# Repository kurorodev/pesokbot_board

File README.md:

# Pesok Robot Board - робототехническая платформа.

## Архитектура

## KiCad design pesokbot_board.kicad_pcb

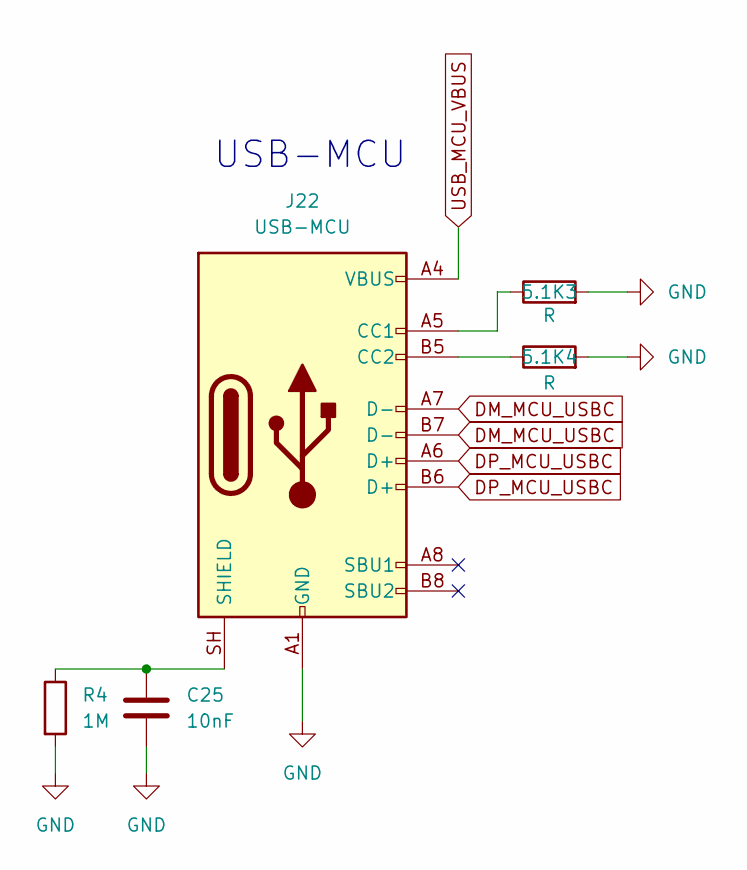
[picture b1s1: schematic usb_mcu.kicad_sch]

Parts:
5.1K3, 5.1K4: R; R_0805_2012Metric_Pad1.20x1.40mm_HandSolder
C25: 10nF; C_0805_2012Metric_Pad1.18x1.45mm_HandSolder
J22: USB-MCU; USB_C_Receptacle_HRO_TYPE-C-31-M-12
R4: 1M; R_0805_2012Metric_Pad1.20x1.40mm_HandSolder

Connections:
DM_MCU_USBC: J22.A7 (D-), J22.B7 (D-)
DP_MCU_USBC: J22.A6 (D+), J22.B6 (D+)
unnamed: 5.1K3.1, J22.A5 (CC1)
unnamed: 5.1K4.1, J22.B5 (CC2)
unnamed: C25.1, J22.SH (SHIELD), R4.1
USB_MCU_VBUS: J22.A4 (VBUS), J22.A9 (VBUS), J22.B4 (VBUS), J22.B9 (VBUS); also elsewhere on the board

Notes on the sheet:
USB-MCU

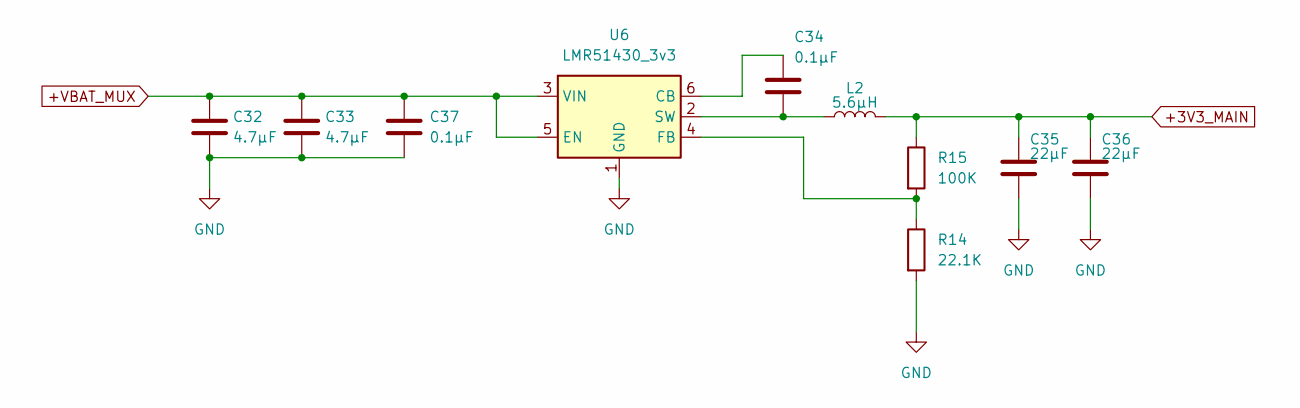
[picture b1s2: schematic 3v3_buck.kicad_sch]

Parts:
C32, C33: 4.7µF; CAPC3216X180N
C34, C37: 0.1µF; CAPC1608X90N
C35, C36: 22µF; CAPC3216X178N
L2: 5.6µH; L_Coilcraft_XAL6060-XXX
R14: 22.1K; R_0201_0603Metric
R15: 100K; R_0201_0603Metric
U6: LMR51430_3v3; SOT-23-6

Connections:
+3V3_MAIN: C35.1, C36.1, L2.2, R15.1
+VBAT_MUX: C32.1, C33.1, C37.1, U6.3 (VIN), U6.5 (EN)
unnamed: C34.1, U6.6 (CB)
unnamed: R14.1, R15.2, U6.4 (FB)
unnamed: C34.2, L2.1, U6.2 (SW)

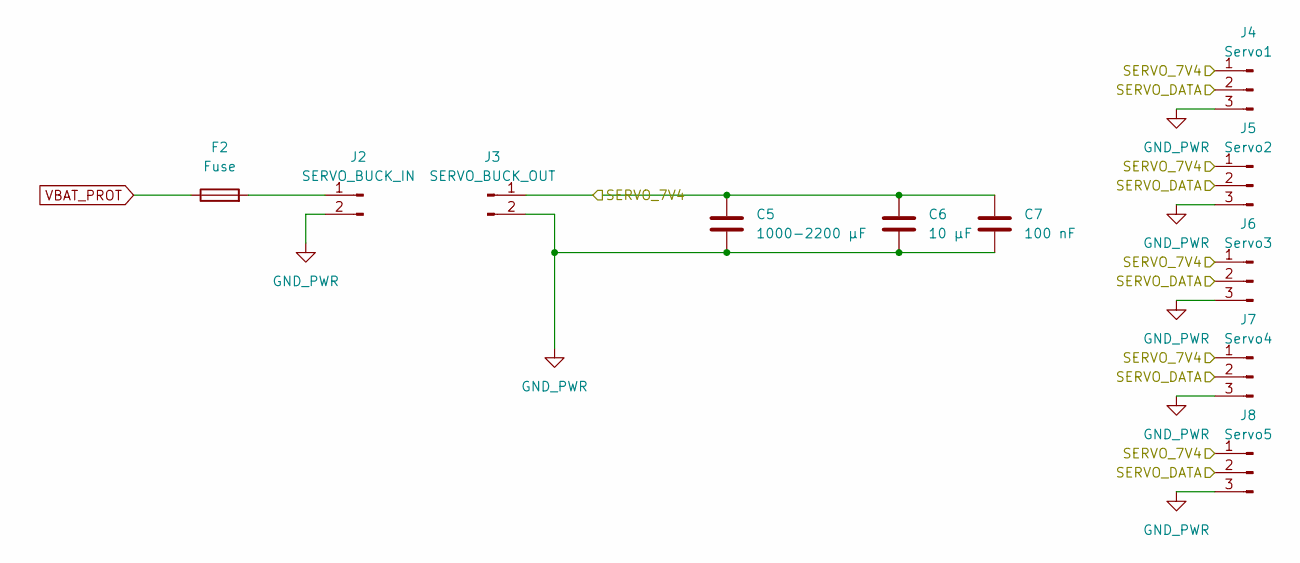
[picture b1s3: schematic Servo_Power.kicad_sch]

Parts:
C5: 1000-2200 µF; C_0805_2012Metric_Pad1.18x1.45mm_HandSolder
C6: 10 µF; C_0805_2012Metric_Pad1.18x1.45mm_HandSolder
C7: 100 nF; CAPC1608X90N
F2: Fuse; Fuse_0805_2012Metric_Pad1.15x1.40mm_HandSolder
J2: SERVO_BUCK_IN
J3: SERVO_BUCK_OUT
J4: Servo1
J5: Servo2
J6: Servo3
J7: Servo4
J8: Servo5

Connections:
GND_PWR: C5.2, C6.2, C7.2, J2.2, J3.2, J4.3, J5.3, J6.3, J7.3, J8.3; also elsewhere on the board
unnamed: C5.1, C6.1, C7.1
unnamed: F2.2, J2.1
unnamed: J3.1, J4.1, J5.1, J6.1, J7.1, J8.1
unnamed: J4.2, J5.2, J6.2, J7.2, J8.2
VBAT_PROT: F2.1; also elsewhere on the board

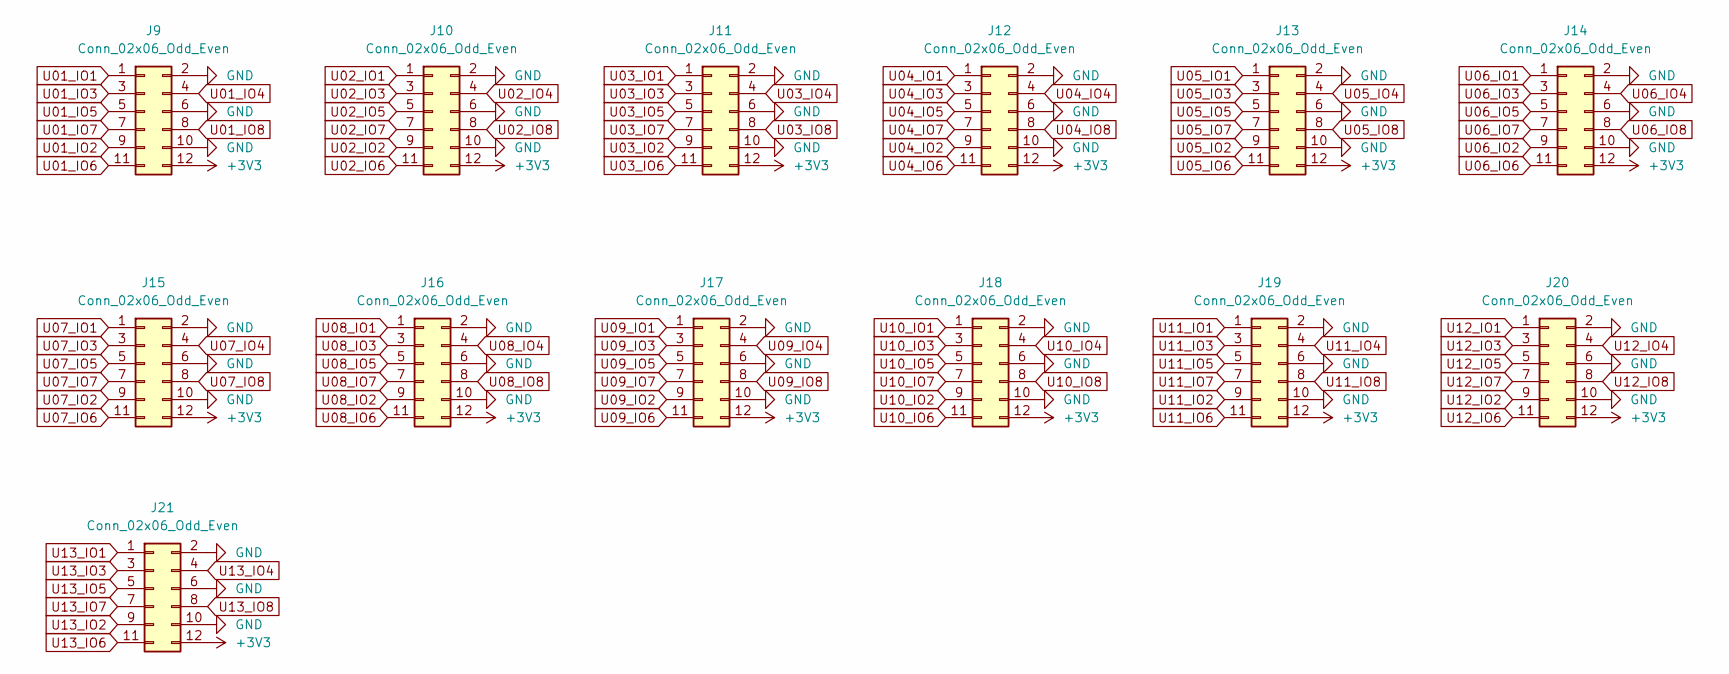
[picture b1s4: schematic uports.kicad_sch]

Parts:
J9, J10, J11, J12, J13, J14, J15, J16, J17, J18, J19, J20, J21: Conn_02x06_Odd_Even; JST_PHD_B12B-PHDSS_2x06_P2.00mm_Vertical

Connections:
+3V3: J9.12, J10.12, J11.12, J12.12, J13.12, J14.12, J15.12, J16.12, J17.12, J18.12, J19.12, J20.12, J21.12; also elsewhere on the board
U01_IO1: J9.1; also elsewhere on the board
U01_IO2: J9.9; also elsewhere on the board
U01_IO3: J9.3; also elsewhere on the board
U01_IO4: J9.4; also elsewhere on the board
U01_IO5: J9.5; also elsewhere on the board
U01_IO6: J9.11; also elsewhere on the board
U01_IO7: J9.7; also elsewhere on the board
U01_IO8: J9.8; also elsewhere on the board
U02_IO1: J10.1; also elsewhere on the board
U02_IO2: J10.9; also elsewhere on the board
U02_IO3: J10.3; also elsewhere on the board
U02_IO4: J10.4; also elsewhere on the board
U02_IO5: J10.5; also elsewhere on the board
U02_IO6: J10.11; also elsewhere on the board
U02_IO7: J10.7; also elsewhere on the board
U02_IO8: J10.8; also elsewhere on the board
U03_IO1: J11.1; also elsewhere on the board
U03_IO2: J11.9; also elsewhere on the board
U03_IO3: J11.3; also elsewhere on the board
U03_IO4: J11.4; also elsewhere on the board
U03_IO5: J11.5; also elsewhere on the board
U03_IO6: J11.11; also elsewhere on the board
U03_IO7: J11.7; also elsewhere on the board
U03_IO8: J11.8; also elsewhere on the board
U04_IO1: J12.1; also elsewhere on the board
U04_IO2: J12.9; also elsewhere on the board
U04_IO3: J12.3; also elsewhere on the board
U04_IO4: J12.4; also elsewhere on the board
U04_IO5: J12.5; also elsewhere on the board
U04_IO6: J12.11; also elsewhere on the board
U04_IO7: J12.7; also elsewhere on the board
U04_IO8: J12.8; also elsewhere on the board
U05_IO1: J13.1; also elsewhere on the board
U05_IO2: J13.9; also elsewhere on the board
U05_IO3: J13.3; also elsewhere on the board
U05_IO4: J13.4; also elsewhere on the board
U05_IO5: J13.5; also elsewhere on the board
U05_IO6: J13.11; also elsewhere on the board
U05_IO7: J13.7; also elsewhere on the board
U05_IO8: J13.8; also elsewhere on the board
U06_IO1: J14.1; also elsewhere on the board
U06_IO2: J14.9; also elsewhere on the board
U06_IO3: J14.3; also elsewhere on the board
U06_IO4: J14.4; also elsewhere on the board
U06_IO5: J14.5; also elsewhere on the board
U06_IO6: J14.11; also elsewhere on the board
U06_IO7: J14.7; also elsewhere on the board
U06_IO8: J14.8; also elsewhere on the board
U07_IO1: J15.1; also elsewhere on the board
U07_IO2: J15.9; also elsewhere on the board
U07_IO3: J15.3; also elsewhere on the board
U07_IO4: J15.4; also elsewhere on the board
U07_IO5: J15.5; also elsewhere on the board
U07_IO6: J15.11; also elsewhere on the board
U07_IO7: J15.7
U07_IO8: J15.8
U08_IO1: J16.1; also elsewhere on the board
U08_IO2: J16.9; also elsewhere on the board
U08_IO3: J16.3; also elsewhere on the board
U08_IO4: J16.4; also elsewhere on the board
U08_IO5: J16.5; also elsewhere on the board
U08_IO6: J16.11; also elsewhere on the board
U08_IO7: J16.7; also elsewhere on the board
U08_IO8: J16.8; also elsewhere on the board
U09_IO1: J17.1; also elsewhere on the board
U09_IO2: J17.9; also elsewhere on the board
U09_IO3: J17.3; also elsewhere on the board
U09_IO4: J17.4; also elsewhere on the board
U09_IO5: J17.5; also elsewhere on the board
U09_IO6: J17.11; also elsewhere on the board
U09_IO7: J17.7; also elsewhere on the board
U09_IO8: J17.8; also elsewhere on the board
U10_IO1: J18.1; also elsewhere on the board
U10_IO2: J18.9; also elsewhere on the board
U10_IO3: J18.3; also elsewhere on the board
U10_IO4: J18.4; also elsewhere on the board
U10_IO5: J18.5; also elsewhere on the board
U10_IO6: J18.11; also elsewhere on the board
U10_IO7: J18.7; also elsewhere on the board
U10_IO8: J18.8; also elsewhere on the board
U11_IO1: J19.1; also elsewhere on the board
U11_IO2: J19.9; also elsewhere on the board
U11_IO3: J19.3; also elsewhere on the board
U11_IO4: J19.4; also elsewhere on the board
U11_IO5: J19.5; also elsewhere on the board
U11_IO6: J19.11; also elsewhere on the board
U11_IO7: J19.7; also elsewhere on the board
U11_IO8: J19.8; also elsewhere on the board
U12_IO1: J20.1; also elsewhere on the board
U12_IO2: J20.9; also elsewhere on the board
U12_IO3: J20.3; also elsewhere on the board
U12_IO4: J20.4; also elsewhere on the board
U12_IO5: J20.5; also elsewhere on the board
U12_IO6: J20.11; also elsewhere on the board
U12_IO7: J20.7; also elsewhere on the board
U12_IO8: J20.8; also elsewhere on the board
U13_IO1: J21.1; also elsewhere on the board
U13_IO2: J21.9; also elsewhere on the board
U13_IO3: J21.3; also elsewhere on the board
U13_IO4: J21.4; also elsewhere on the board
U13_IO5: J21.5; also elsewhere on the board
U13_IO6: J21.11; also elsewhere on the board
U13_IO7: J21.7; also elsewhere on the board
U13_IO8: J21.8; also elsewhere on the board

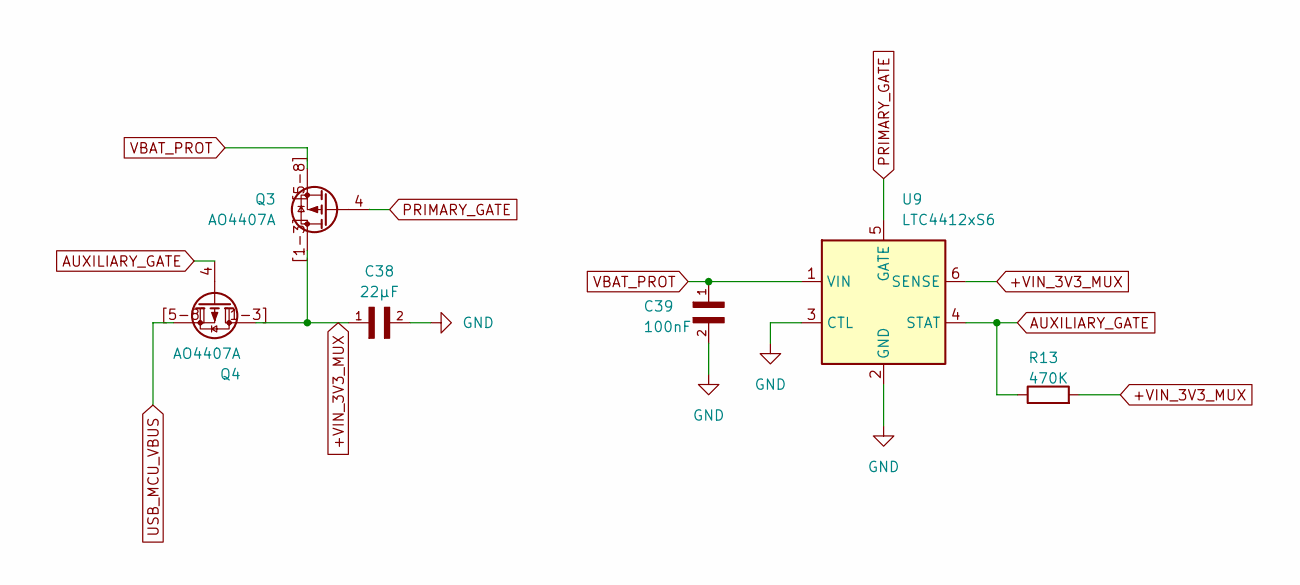
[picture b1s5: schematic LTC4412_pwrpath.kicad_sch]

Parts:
C38: 22µF; CAPC1608X90N
C39: 100nF; CAPC1608X90N
Q3, Q4: AO4407A; SOIC-8_3.9x4.9mm_P1.27mm
R13: 470K
U9: LTC4412xS6; TSOT-23-6

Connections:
+VIN_3V3_MUX: C38.1, Q3.1 (Source), Q3.2 (Source), Q3.3 (Source), Q3.[1-3] (Source), Q4.1 (Source), Q4.2 (Source), Q4.3 (Source), Q4.[1-3] (Source), R13.2, U9.6 (SENSE)
AUXILIARY_GATE: Q4.4 (Gate), R13.1, U9.4 (STAT)
PRIMARY_GATE: Q3.4 (Gate), U9.5 (GATE)
USB_MCU_VBUS: Q4.5 (Drain), Q4.6 (Drain), Q4.7 (Drain), Q4.8 (Drain); also elsewhere on the board
VBAT_PROT: C39.1, Q3.5 (Drain), Q3.6 (Drain), Q3.7 (Drain), Q3.8 (Drain), Q3.[5-8] (Drain), U9.1 (VIN); also elsewhere on the board

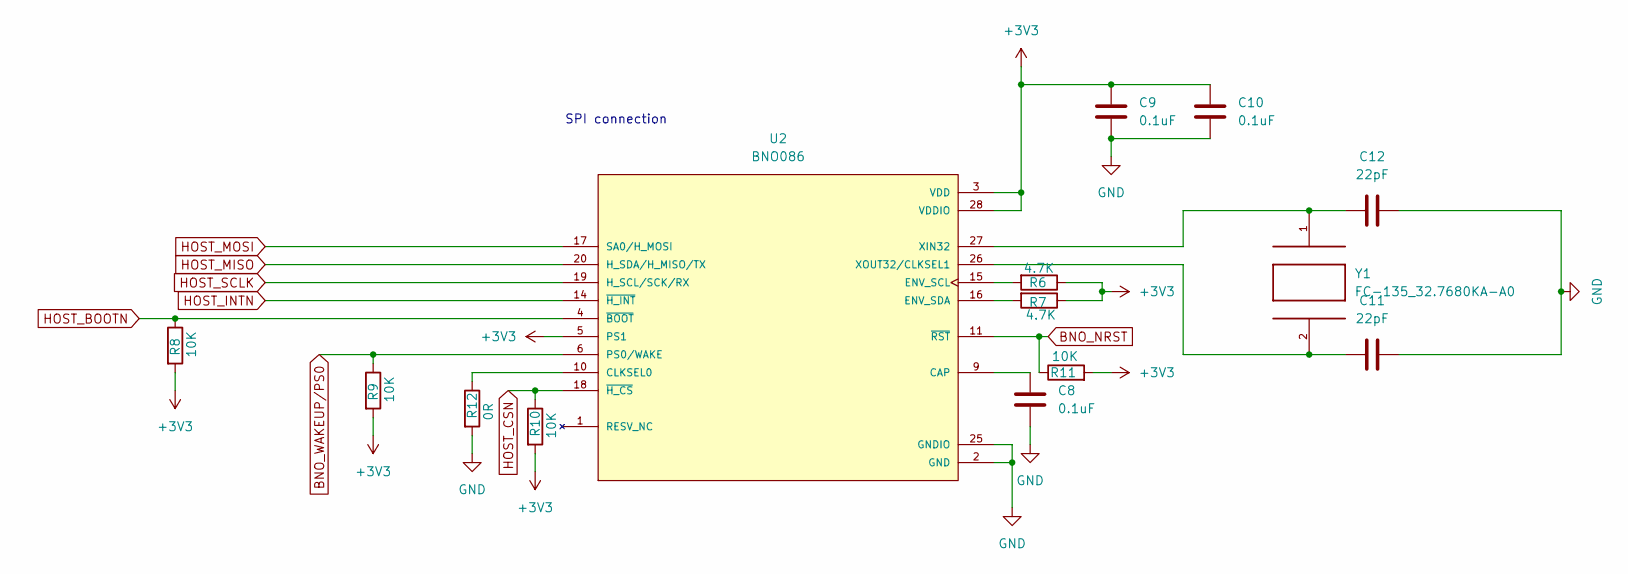
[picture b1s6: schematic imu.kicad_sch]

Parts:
C8, C9, C10: 0.1uF; C_0805_2012Metric_Pad1.18x1.45mm_HandSolder
C11, C12: 22pF; C_0805_2012Metric_Pad1.18x1.45mm_HandSolder
R6, R7: 4.7K; R_0805_2012Metric_Pad1.20x1.40mm_HandSolder
R8, R9, R10, R11: 10K; R_0805_2012Metric_Pad1.20x1.40mm_HandSolder
R12: 0R; R_0805_2012Metric_Pad1.20x1.40mm_HandSolder
U2: BNO086; IC_BNO086; PARTREV v1.17
Y1: FC-135_32.7680KA-A0; XTAL_FC-135_32.7680KA-A0

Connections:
+3V3: C9.1, C10.1, R6.1, R7.1, R8.2, R9.2, R10.2, R11.2, U2.3 (VDD), U2.5 (PS1), U2.28 (VDDIO); also elsewhere on the board
BNO_NRST: R11.1, U2.11 (~RST); also elsewhere on the board
BNO_WAKEUP/PS0: R9.1, U2.6 (PS0/WAKE); also elsewhere on the board
HOST_BOOTN: R8.1, U2.4 (~BOOT); also elsewhere on the board
HOST_CSN: R10.1, U2.18 (~H_CS); also elsewhere on the board
HOST_INTN: U2.14 (~H_INT); also elsewhere on the board
HOST_MISO: U2.20 (H_SDA/H_MISO/TX); also elsewhere on the board
HOST_MOSI: U2.17 (SA0/H_MOSI); also elsewhere on the board
HOST_SCLK: U2.19 (H_SCL/SCK/RX); also elsewhere on the board
unnamed: C8.1, U2.9 (CAP)
unnamed: R12.1, U2.10 (CLKSEL0)
unnamed: R6.2, U2.15 (ENV_SCL)
unnamed: R7.2, U2.16 (ENV_SDA)
unnamed: C12.2, U2.27 (XIN32), Y1.1
unnamed: C11.1, U2.26 (XOUT32/CLKSEL1), Y1.2

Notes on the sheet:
SPI connection

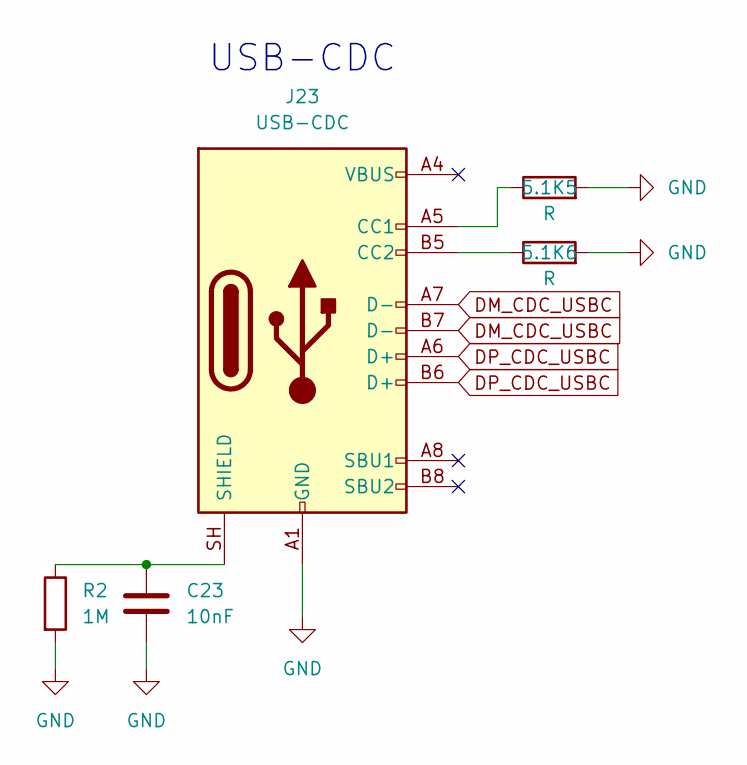
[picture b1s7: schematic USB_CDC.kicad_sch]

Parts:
5.1K5, 5.1K6: R; R_0805_2012Metric_Pad1.20x1.40mm_HandSolder
C23: 10nF; C_0805_2012Metric_Pad1.18x1.45mm_HandSolder
J23: USB-CDC; USB_C_Receptacle_HRO_TYPE-C-31-M-12
R2: 1M; R_0805_2012Metric_Pad1.20x1.40mm_HandSolder

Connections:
DM_CDC_USBC: J23.A7 (D-), J23.B7 (D-)
DP_CDC_USBC: J23.A6 (D+), J23.B6 (D+)
unnamed: 5.1K5.1, J23.A5 (CC1)
unnamed: 5.1K6.1, J23.B5 (CC2)
unnamed: C23.1, J23.SH (SHIELD), R2.1

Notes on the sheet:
USB-CDC

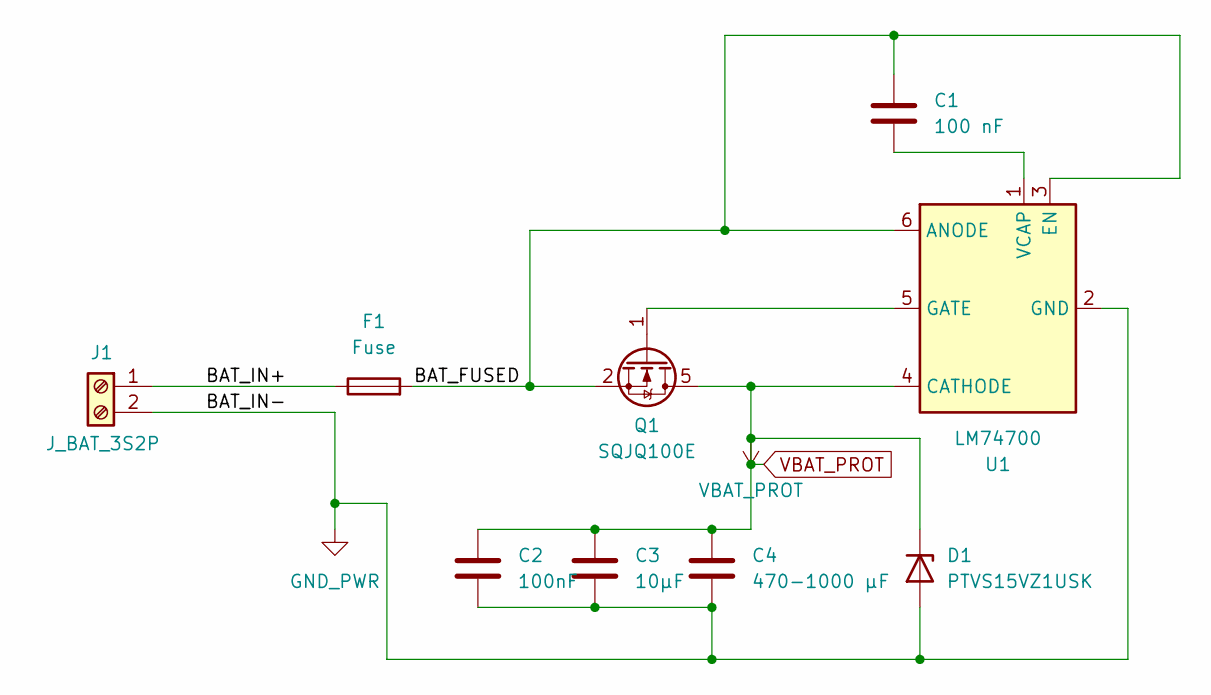
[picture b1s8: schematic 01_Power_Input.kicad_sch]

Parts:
C1: 100 nF; CAPC1608X90N
C2: 100nF; CAPC1608X90N
C3: 10µF; C_0805_2012Metric_Pad1.18x1.45mm_HandSolder
C4: 470-1000 µF; C_0805_2012Metric_Pad1.18x1.45mm_HandSolder
D1: PTVS15VZ1USK; Nexperia_DSN1608-2_1.6x0.8mm
F1: Fuse; Fuse_0805_2012Metric_Pad1.15x1.40mm_HandSolder
J1: J_BAT_3S2P; TerminalBlock_Phoenix_MKDS-1,5-2-5.08_1x02_P5.08mm_Horizont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
Q1: SQJQ100E; LFPAK88
U1: LM74700; SOT-23-6

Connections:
/01_Power_Input/BAT_FUSED: C1.1, F1.2, Q1.2 (S), Q1.3 (S), Q1.4 (S), U1.3 (EN), U1.6 (ANODE)
/01_Power_Input/BAT_IN+: F1.1, J1.1
GND_PWR: C2.2, C3.2, C4.2, D1.2 (A), J1.2, U1.2 (GND); also elsewhere on the board
unnamed: Q1.1 (G), U1.5 (GATE)
unnamed: C1.2, U1.1 (VCAP)
VBAT_PROT: C2.1, C3.1, C4.1, D1.1 (K), Q1.5 (D), U1.4 (CATHODE); also elsewhere on the board

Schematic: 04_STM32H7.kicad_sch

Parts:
C13, C17, C19, C20, C22: 100nF; CAPC1608X90N
C14: 10 µF; C_0805_2012Metric_Pad1.18x1.45mm_HandSolder
C15, C16: 2.2 µF; C_0805_2012Metric_Pad1.18x1.45mm_HandSolder
C18: 1 µF; C_0805_2012Metric_Pad1.18x1.45mm_HandSolder
C21: 4.7 µF; C_0805_2012Metric_Pad1.18x1.45mm_HandSolder
R1: R; R_0805_2012Metric_Pad1.20x1.40mm_HandSolder
U3: STM32H743ZIT6; QFP50P2200X2200X160; PARTREV 7
U4: REF3033; SOT-23

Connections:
+3V3: C13.2, C14.2, C19.2, C20.1, C22.2, R1.1, U3.6 (VBAT), U3.17 (VDD), U3.30 (VDD), U3.39 (VDD), U3.52 (VDD), U3.62 (VDD), U3.72 (VDD), U3.84 (VDD), U3.95 (VDD33USB), U3.108 (VDD), U3.121 (VDD), U3.131 (VDD), U3.144 (VDD), U4.1 (IN); also elsewhere on the board
BNO_NRST: U3.69 (PB10); also elsewhere on the board
BNO_WAKEUP/PS0: U3.48 (PB2); also elsewhere on the board
DM_USBC: U3.103 (PA11)
DP_USBC: U3.104 (PA12)
HOST_BOOTN: U3.47 (PB1); also elsewhere on the board
HOST_CSN: U3.40 (PA4); also elsewhere on the board
HOST_INTN: U3.46 (PB0); also elsewhere on the board
HOST_MISO: U3.42 (PA6); also elsewhere on the board
HOST_MOSI: U3.43 (PA7); also elsewhere on the board
HOST_SCLK: U3.41 (PA5); also elsewhere on the board
unnamed: C17.2, C18.2, R1.2, U3.33 (VDDA)
U01_IO1: U3.34 (PA0); also elsewhere on the board
U01_IO2: U3.35 (PA1); also elsewhere on the board
U01_IO3: U3.36 (PA2); also elsewhere on the board
U01_IO4: U3.37 (PA3); also elsewhere on the board
U01_IO5: U3.100 (PA8); also elsewhere on the board
U01_IO6: U3.101 (PA9); also elsewhere on the board
U01_IO7: U3.102 (PA10); also elsewhere on the board
U01_IO8: U3.110 (PA15(JTDI)); also elsewhere on the board
U02_IO1: U3.133 (PB3(JTDO/TRACESWO)); also elsewhere on the board
U02_IO2: U3.134 (PB4(~JTRST)); also elsewhere on the board
U02_IO3: U3.135 (PB5); also elsewhere on the board
U02_IO4: U3.136 (PB6); also elsewhere on the board
U02_IO5: U3.137 (PB7); also elsewhere on the board
U02_IO6: U3.139 (PB8); also elsewhere on the board
U02_IO7: U3.140 (PB9); also elsewhere on the board
U02_IO8: U3.70 (PB11); also elsewhere on the board
U03_IO1: U3.73 (PB12); also elsewhere on the board
U03_IO2: U3.74 (PB13); also elsewhere on the board
U03_IO3: U3.75 (PB14); also elsewhere on the board
U03_IO4: U3.76 (PB15); also elsewhere on the board
U03_IO5: U3.114 (PD0); also elsewhere on the board
U03_IO6: U3.115 (PD1); also elsewhere on the board
U03_IO7: U3.116 (PD2); also elsewhere on the board
U03_IO8: U3.117 (PD3); also elsewhere on the board
U04_IO1: U3.26 (PC0); also elsewhere on the board
U04_IO2: U3.27 (PC1); also elsewhere on the board
U04_IO3: U3.28 (PC2_C); also elsewhere on the board
U04_IO4: U3.29 (PC3_C); also elsewhere on the board
U04_IO5: U3.44 (PC4); also elsewhere on the board
U04_IO6: U3.45 (PC5); also elsewhere on the board
U04_IO7: U3.96 (PC6); also elsewhere on the board
U04_IO8: U3.97 (PC7); also elsewhere on the board
U05_IO1: U3.98 (PC8); also elsewhere on the board
U05_IO2: U3.99 (PC9); also elsewhere on the board
U05_IO3: U3.111 (PC10); also elsewhere on the board
U05_IO4: U3.112 (PC11); also elsewhere on the board
U05_IO5: U3.113 (PC12); also elsewhere on the board
U05_IO6: U3.7 (PC13); also elsewhere on the board
U05_IO7: U3.8 (PC14/OSC32_IN); also elsewhere on the board
U05_IO8: U3.9 (PC15/OSC32_OUT); also elsewhere on the board
U06_IO1: U3.118 (PD4); also elsewhere on the board
U06_IO2: U3.119 (PD5); also elsewhere on the board
U06_IO3: U3.122 (PD6); also elsewhere on the board
U06_IO4: U3.123 (PD7); also elsewhere on the board
U06_IO5: U3.77 (PD8); also elsewhere on the board
U06_IO6: U3.78 (PD9); also elsewhere on the board
U06_IO7: U3.79 (PD10); also elsewhere on the board
U06_IO8: U3.80 (PD11); also elsewhere on the board
U07_IO1: U3.81 (PD12); also elsewhere on the board
U07_IO2: U3.82 (PD13); also elsewhere on the board
U07_IO3: U3.85 (PD14); also elsewhere on the board
U07_IO4: U3.86 (PD15); also elsewhere on the board
U07_IO5: U3.23 (PH0/OSC_IN); also elsewhere on the board
U07_IO6: U3.24 (PH1/OSC_OUT); also elsewhere on the board
U08_IO1: U3.141 (PE0); also elsewhere on the board
U08_IO2: U3.1 (PE2); also elsewhere on the board
U08_IO3: U3.142 (PE1); also elsewhere on the board
U08_IO4: U3.2 (PE3); also elsewhere on the board
U08_IO5: U3.3 (PE4); also elsewhere on the board
U08_IO6: U3.4 (PE5); also elsewhere on the board
U08_IO7: U3.5 (PE6); also elsewhere on the board
U08_IO8: U3.58 (PE7); also elsewhere on the board
U09_IO1: U3.59 (PE8); also elsewhere on the board
U09_IO2: U3.60 (PE9); also elsewhere on the board
U09_IO3: U3.63 (PE10); also elsewhere on the board
U09_IO4: U3.64 (PE11); also elsewhere on the board
U09_IO5: U3.65 (PE12); also elsewhere on the board
U09_IO6: U3.66 (PE13); also elsewhere on the board
U09_IO7: U3.67 (PE14); also elsewhere on the board
U09_IO8: U3.68 (PE15); also elsewhere on the board
U10_IO1: U3.10 (PF0); also elsewhere on the board
U10_IO2: U3.11 (PF1); also elsewhere on the board
U10_IO3: U3.12 (PF2); also elsewhere on the board
U10_IO4: U3.13 (PF3); also elsewhere on the board
U10_IO5: U3.14 (PF4); also elsewhere on the board
U10_IO6: U3.15 (PF5); also elsewhere on the board
U10_IO7: U3.54 (PF14); also elsewhere on the board
U10_IO8: U3.55 (PF15); also elsewhere on the board
U11_IO1: U3.18 (PF6); also elsewhere on the board
U11_IO2: U3.19 (PF7); also elsewhere on the board
U11_IO3: U3.20 (PF8); also elsewhere on the board
U11_IO4: U3.21 (PF9); also elsewhere on the board
U11_IO5: U3.22 (PF10); also elsewhere on the board
U11_IO6: U3.49 (PF11); also elsewhere on the board
U11_IO7: U3.50 (PF12); also elsewhere on the board
U11_IO8: U3.53 (PF13); also elsewhere on the board
U12_IO1: U3.56 (PG0); also elsewhere on the board
U12_IO2: U3.57 (PG1); also elsewhere on the board
U12_IO3: U3.87 (PG2); also elsewhere on the board
U12_IO4: U3.88 (PG3); also elsewhere on the board
U12_IO5: U3.89 (PG4); also elsewhere on the board
U12_IO6: U3.90 (PG5); also elsewhere on the board
U12_IO7: U3.91 (PG6); also elsewhere on the board
U12_IO8: U3.92 (PG7); also elsewhere on the board
U13_IO1: U3.93 (PG8); also elsewhere on the board
U13_IO2: U3.124 (PG9); also elsewhere on the board
U13_IO3: U3.125 (PG10); also elsewhere on the board
U13_IO4: U3.126 (PG11); also elsewhere on the board
U13_IO5: U3.127 (PG12); also elsewhere on the board
U13_IO6: U3.128 (PG13); also elsewhere on the board
U13_IO7: U3.129 (PG14); also elsewhere on the board
U13_IO8: U3.132 (PG15); also elsewhere on the board
VCAP: C15.2, C16.2, U3.71 (VCAP), U3.106 (VCAP)
ref3033: C21.1, U3.32 (VREF+), U4.2 (OUT)

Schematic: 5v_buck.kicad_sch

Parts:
C24, C26: 100 nF; CAPC1608X90N
C27, C28: 4.7uF; CAPC3216X180N
C29, C30, C31: 22uF; CAPC3216X178N
L1: 6.8uH; L_Coilcraft_XAL6060-XXX
R3: 100K; R_0201_0603Metric
R5: 13.7K; R_0201_0603Metric
U5: LMR51430_5v; SOT-23-6

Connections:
+5V_MAIN: C30.1, C31.1, L1.2, R3.1
unnamed: R3.2, R5.1, U5.4 (FB)
VBAT_PROT: C26.1, C27.1, C28.1, C29.1, U5.3 (VIN), U5.5 (EN); also elsewhere on the board

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
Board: 4 copper layers, 93 parts (0 on the bottom side), 152 nets, no tracks yet.

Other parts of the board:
5.1K1, 5.1K2: R; R_0805_2012Metric_Pad1.20x1.40mm_HandSolder
C24#2: 100 nF; CAPC1608X90N
R3#2: 1M; R_0805_2012Metric_Pad1.20x1.40mm_HandSolder
